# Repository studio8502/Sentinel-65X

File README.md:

# Sentinel 65X

This is a design for an 8/16-bit computer/games console, which uses
the 65816 CPU architecture (by WDC) and the VERA video system (by
Frank van den Hoef) as its core. It is not directly compatible with
any existing system, but porting from other 6502 and 65816 systems
which have a similar architecture should not prove difficult.

## Features

- Designed to minimize BOM and construction costs
- Intended to be a turnkey "fabrication ready" design which anyone
  can produce and sell for any purpose
- Fully open source hardware designs, released under the CERN OHL
  (permissive) V2
- 8MHz WDC W65C265S CPU (W65C816S compatible)
  - 16MB adress space
  - 8 timers
  - Multiple priority-encoded interrupts
  - Built-in GPIO
- 512KB of on-board static RAM
- 512KB of flash ROM
- RGB video output at 640x480
- Stereo audio output
- SD card slot
- Dual enhanced SNES-compatible controller ports
  - Supports SNES controllers & joysticks
  - Supports the SNES mouse and clones
  - Enhanced with I2C bus support for custom peripherals
- Cartridge/expansion port with full system bus, supporting ROM,
  RAM, and I/O expansions
- Amiga-inspired "clock port" which also serves as a debug port

## Hardware

The revision 0 schematic is nearly finished, approaching the production
of the first working prototypes. The goal is a limited release in 2024,
followed by a full release in 2025.

## Software

At the present time, software for this design is nonexistent. The
intention is to implement a kernel and library to support assembly
and C programming for cross-development (using the Calypsi C toolchain),
and to eventually develop or port a suite of tools for on-device
programming to be put into the system ROM.

The planned kernel will be reminiscent of the architecture of MSX-DOS
2, but will support long file names and the FAT32 (and later ExFAT)
filesystem on SD cards.

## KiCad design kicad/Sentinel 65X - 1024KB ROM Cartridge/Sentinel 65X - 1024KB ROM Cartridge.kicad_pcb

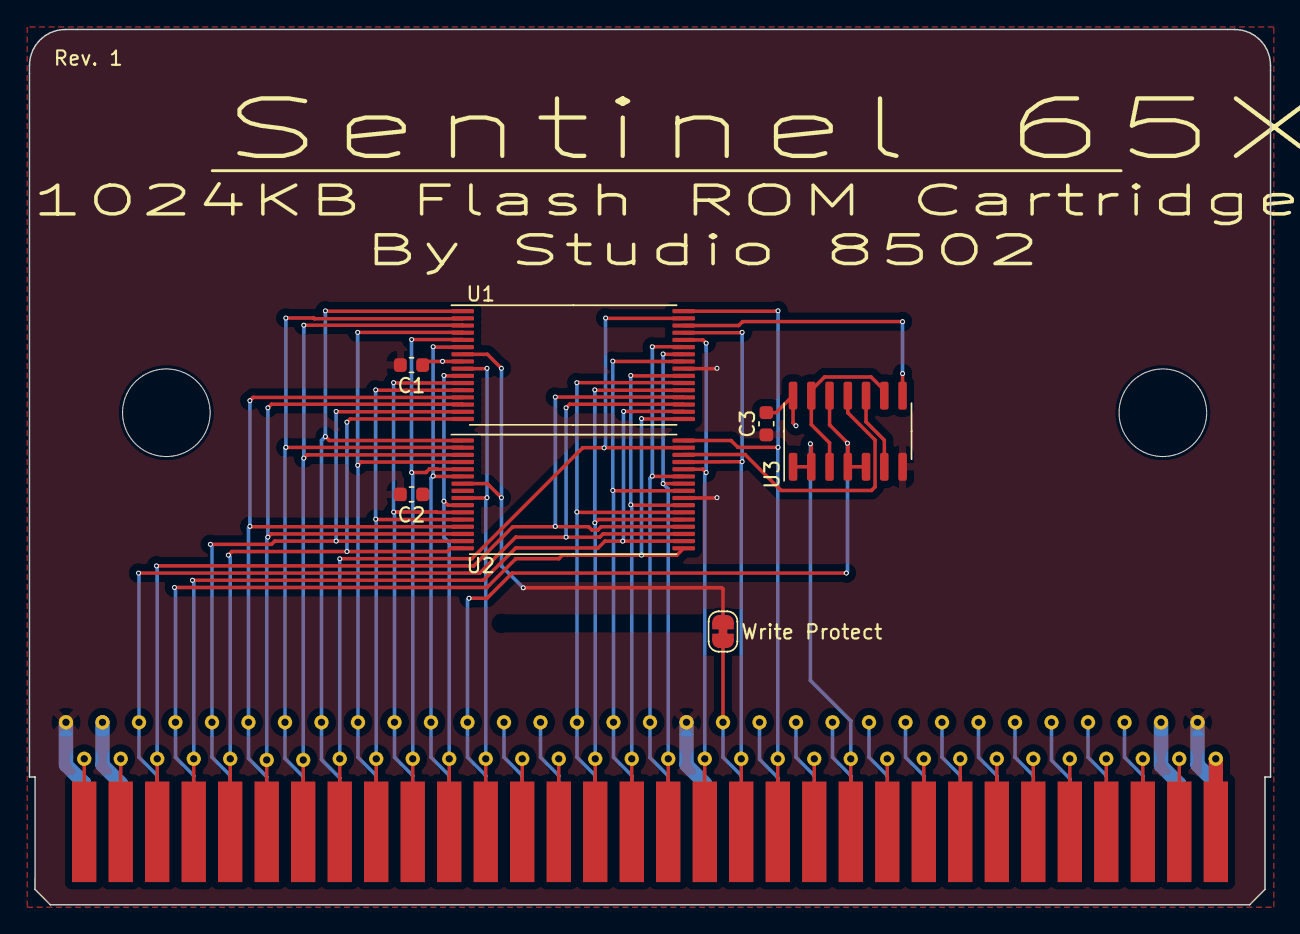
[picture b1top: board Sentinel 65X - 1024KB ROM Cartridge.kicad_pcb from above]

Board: 2 copper layers, 86.4 x 60.9 mm, 8 parts (0 on the bottom side), 38 nets.

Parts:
C1, C2, C3: 100nF; C_0603_1608Metric
J1: 2x32 2.54mm Card Edge Connector; Conn_Edge_2x32_THT_2.54mm_Male
JP1: SolderJumper_2_Bridged; SolderJumper-2_P1.3mm_Bridged_RoundedPad1.0x1.5mm
U1, U2: TSOP-I-32_14.4x8mm_P0.5mm
U3: 74LS00; SOIC-14_3.9x8.7mm_P1.27mm

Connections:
+3.3V: C1.1, C2.1, C3.1, J1.a2, J1.a31, U1.8 (VDD), U2.8 (VDD), U3.14 (VCC)
/A0: J1.b30, U1.20 (A0), U2.20 (A0)
/A1: J1.a30, U1.19 (A1), U2.19 (A1)
/A2: J1.b29, U1.18 (A2), U2.18 (A2)
/A3: J1.a29, U1.17 (A3), U2.17 (A3)
/A4: J1.b28, U1.16 (A4), U2.16 (A4)
/A5: J1.a28, U1.15 (A5), U2.15 (A5)
/A6: J1.b27, U1.14 (A6), U2.14 (A6)
/A7: J1.a27, U1.13 (A7), U2.13 (A7)
/A8: J1.b26, U1.3 (A8), U2.3 (A8)
/A9: J1.a26, U1.2 (A9), U2.2 (A9)
/A10: J1.b25, U1.31 (A10), U2.31 (A10)
/A11: J1.a25, U1.1 (A11), U2.1 (A11)
/A12: J1.b24, U1.12 (A12), U2.12 (A12)
/A13: J1.a24, U1.4 (A13), U2.4 (A13)
/A14: J1.b23, U1.5 (A14), U2.5 (A14)
/A15: J1.a23, U1.11 (A15), U2.11 (A15)
/A16: J1.b22, U1.10 (A16), U2.10 (A16)
/A17: J1.a22, U1.6 (A17), U2.6 (A17)
/A18: J1.b21, U1.9 (A18), U2.9 (A18)
/A19: J1.a21, U3.4, U3.5, U3.12
/D0: J1.b18, U1.21 (D0), U2.21 (D0)
/D1: J1.a18, U1.22 (D1), U2.22 (D1)
/D2: J1.b17, U1.23 (D2), U2.23 (D2)
/D3: J1.a17, U1.25 (D3), U2.25 (D3)
/D4: J1.b16, U1.26 (D4), U2.26 (D4)
/D5: J1.a16, U1.27 (D5), U2.27 (D5)
/D6: J1.b15, U1.28 (D6), U2.28 (D6)
/D7: J1.b14, U1.29 (D7), U2.29 (D7)
/~CS6: J1.b11, U3.1, U3.2
/~RD: J1.b13, U1.32 (~OE), U2.32 (~OE)
/~ROMH: U2.30 (~CE), U3.11
/~ROML: U1.30 (~CE), U3.8
/~WR: JP1.2 (B), U1.7 (~WE), U2.7 (~WE)
GND: C1.2, C2.2, C3.2, J1.a1, J1.a15, J1.a32, U1.24 (GND), U2.24 (GND), U3.7 (GND)
unnamed: J1.a14, JP1.1 (A)
unnamed: U3.6, U3.10
unnamed: U3.3, U3.9, U3.13

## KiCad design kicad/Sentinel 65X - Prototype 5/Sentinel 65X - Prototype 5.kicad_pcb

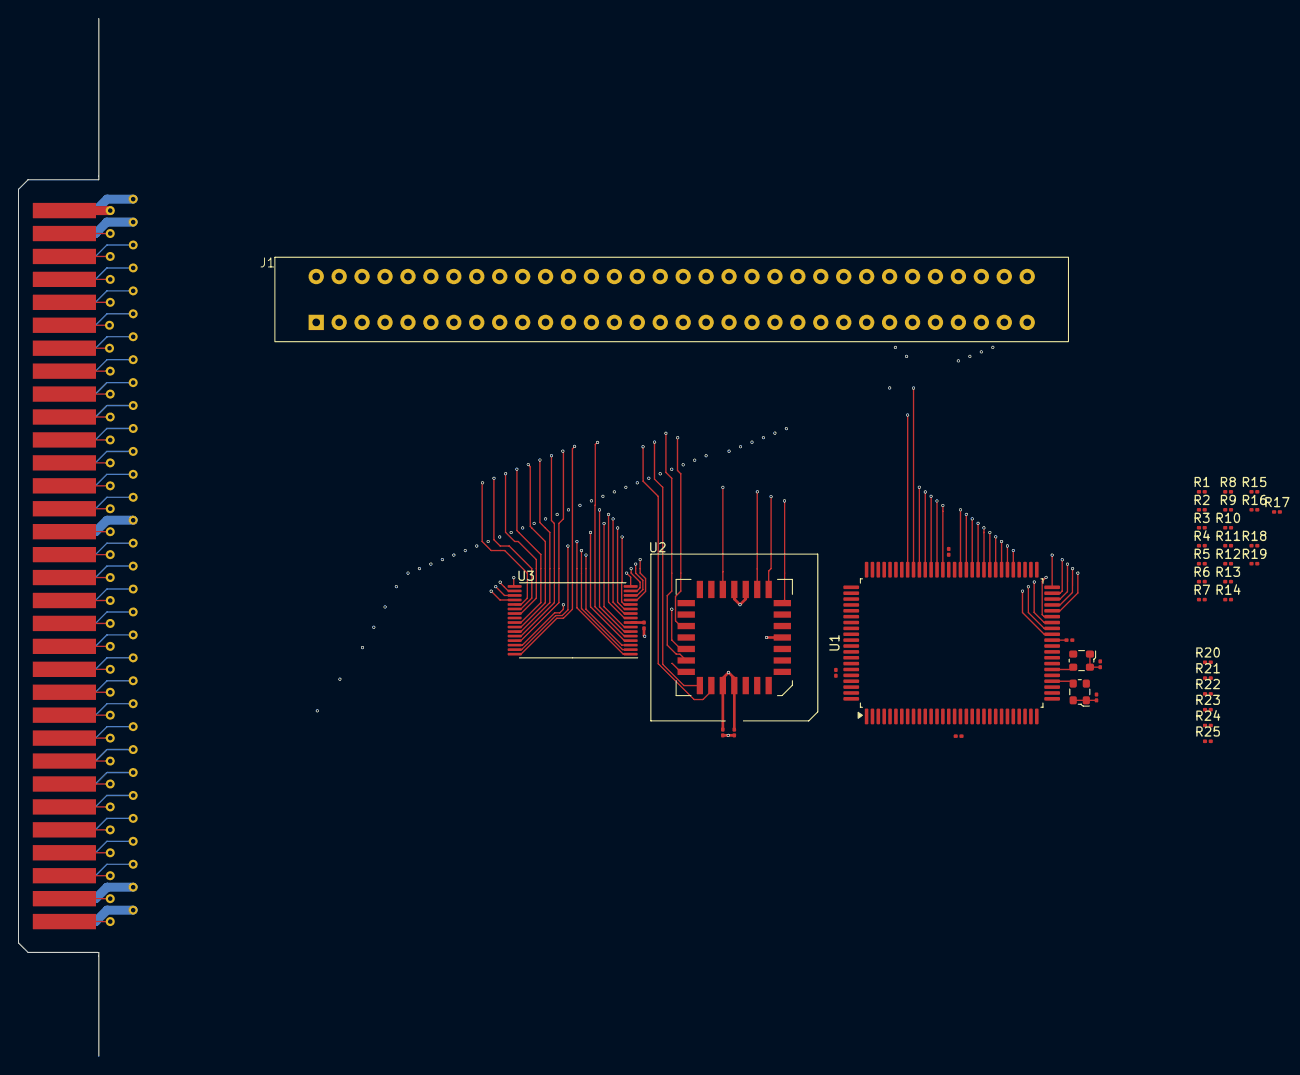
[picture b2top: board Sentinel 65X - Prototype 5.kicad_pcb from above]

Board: 6 copper layers, 41 parts (0 on the bottom side), 69 nets.

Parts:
C1, C2, C3, C4, C5, C6, C7, C8, C9: 100nF; C_0201_0603Metric
J1: 2x32 2.54mm Card Edge Connector; Conn_Edge_2x32p_THT_2.54mm_5.08mm
J2: 2x32 2.54mm Card Edge Connector; Conn_Edge_2x32_THT_2.54mm_Male
R1, R2, R3, R4, R5, R6, R7, R8, R9, R10, R11, R12, R13, R14, R15, R16, R17, R18, R19, R20, R21, R22, R23, R24, R25: 3.3KΩ; R_0201_0603Metric
U1: W65C265S8QG-8; PQFP-100_14x20mm_P0.65mm
U2: ATF22LV10C-10JU; PLCC-28_SMD-Socket
U3: IS61C5128AS-25HLI; TSOP-I-32_11.8x8mm_P0.5mm
X1: 520-327MVATX-2-CNTR3; Oscillator_SMD_ECS_2520MV-xxx-xx-4Pin_2.5x2.0mm
X2: KC2520Z8.00000C1KX00; Oscillator_SMD_ECS_2520MV-xxx-xx-4Pin_2.5x2.0mm

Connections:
+3.3V: C1.1, C2.1, C3.1, C4.1, C5.1, C6.1, C7.1, C8.1, C9.1, J1.a2, J1.a31, J2.a2, J2.a31, R1.1, R2.1, R3.1, R4.1, R5.2, R6.2, R7.2, R8.2, R9.2, R10.2, R11.2, R12.2, R13.2, R14.2, R15.2, R16.2, R17.2, R18.2, R19.2, R20.2, R21.2, R22.2, R23.2, R24.2, R25.2, U1.14 (VDD), U1.41 (VDD), U1.66 (VDD), U1.89 (VDD), U2.1 (VCC), U2.28 (VCC), U3.8 (VDD), X1.1 (EN), X1.4 (V+), X2.1 (EN), X2.4 (V+)
+5V: J1.b32, J2.b32
/A0: J1.b3, J2.b3, U1.42 (A0), U3.20 (A0)
/A1: J1.a3, J2.a3, U1.43 (A1), U3.19 (A1)
/A2: J1.b4, J2.b4, U1.44 (A2), U3.18 (A2)
/A3: J1.a4, J2.a4, U1.45 (A3), U3.17 (A3)
/A4: J1.b5, J2.b5, U1.46 (A4), U3.16 (A4)
/A5: J1.a5, J2.a5, U1.47 (A5), U3.15 (A5)
/A6: J1.b6, J2.b6, U1.48 (A6), U3.14 (A6)
/A7: J1.a6, J2.a6, U1.49 (A7), U3.13 (A7)
/A8: J1.b7, J2.b7, U1.50 (A8), U3.3 (A8)
/A9: J1.a7, J2.a7, U1.55 (A9), U3.2 (A9)
/A10: J1.b8, J2.b8, U1.56 (A10), U3.31 (A10)
/A11: J1.a8, J2.a8, U1.57 (A11), U3.1 (A11)
/A12: J1.b9, J2.b9, U1.58 (A12), U3.12 (A12)
/A13: J1.a9, J2.a9, U1.59 (A13), U3.4 (A13)
/A14: J1.b10, J2.b10, U1.60 (A14), U3.11 (A14)
/A15: J1.a10, J2.a10, U1.61 (A15), U3.7 (A15)
/A16: J1.b11, J2.b11, U1.62 (A16), U3.10 (A16)
/A17: J1.a11, J2.a11, U1.63 (A17), U3.9 (A17)
/A18: J1.b12, J2.b12, U1.64 (A18), U3.6 (A18)
/A19: J1.a12, J2.a12, U1.67 (A19), U2.10 (IN)
/A20: J1.b13, J2.b13, U1.68 (A20), U2.11 (IN)
/A21: J1.a13, J2.a13, U1.69 (A21), U2.12 (IN)
/A22: J1.b14, J2.b14, U1.70 (A22), U2.13 (IN)
/A23: J1.a14, J2.a14, U1.71 (A23), U2.16 (IN)
/BA: J1.b24, J2.b24, R6.1, U1.39 (BA)
/BE: J1.a21, J2.a21, R4.2, U1.35 (BE)
/CDONE: R15.1, U1.99 (P43)
/CLK: U1.36 (CLK), X1.3 (OUT)
/D0: J1.b15, J2.b15, U1.84 (D0), U3.21 (I/O0)
/D1: J1.a15, J2.a15, U1.85 (D1), U3.22 (I/O1)
/D2: J1.b16, J2.b16, U1.86 (D2), U3.23 (I/O2)
/D3: J1.a16, J2.a16, U1.87 (D3), U3.25 (I/O3)
/D4: J1.b17, J2.b17, U1.88 (D4), U3.26 (I/O4)
/D5: J1.a17, J2.a17, U1.91 (D5), U3.27 (I/O5)
/D6: J1.b18, J2.b18, U1.92 (D6), U3.28 (I/O6)
/D7: J1.b19, J2.b19, U1.93 (D7), U3.29 (I/O7)
/FCLK: U1.34 (FCLK), X2.3 (OUT)
/I2C_SCL: J1.a27, J2.a27, R17.1, U1.7 (P47)
/I2C_SDA: J1.a28, J2.a28, R16.1, U1.6 (P46)
/PHI2: J1.b1, J2.b1, U1.38 (PHI2), U2.2 (CLK/IN)
/RUN: J1.a23, J2.a23, R5.1, U1.32 (RUN)
/R/~W: J1.b25, J2.b25, R7.1, U1.31 (~WE), U2.3 (IN)
/SNES_CLK: J1.a30, J2.a30, U1.8 (P50)
/SNES_DATA0: J1.b27, J2.b27, U1.10 (P52)
/SNES_DATA1: J1.b28, J2.b28, U1.11 (P53)
/SNES_DATA2: J1.b29, J2.b29
/SNES_DATA3: J1.b30, J2.b30
/SNES_LATCH: J1.a29, J2.a29, U1.9 (P51)
/~BOOT_SEL: R18.1, U1.21 (P63)
/~CS4: R10.1, U1.80 (~CS4), U2.9 (IN)
/~CS5: R11.1, U1.81 (~CS5), U2.7 (IN)
/~CS6: J1.b22, J2.b22, R12.1, U1.82 (~CS6), U2.6 (IN)
/~CS7: J1.a22, J2.a22, R13.1, U1.83 (~CS7)
/~FPGA_RESET: R14.1, U1.98 (P42)
/~IRQ: J1.a24, J2.a24, R2.2, U1.97 (~IRQ)
/~I/O0: J1.b26, J2.b26, R8.1, U1.72 (~CS0)
/~I/O1: J1.b23, J2.b23, R9.1, U1.73 (~CS1)
/~NMI: J1.a26, J2.a26, R3.2, U1.96 (~NMI)
/~RAM0: R21.1, U2.23 (I/O), U3.30 (~CE)
/~RAM1: J1.a20, J2.a20, R20.1, U2.21 (I/O)
/~RD: J1.b20, J2.b20, R24.1, U2.26 (I/O), U3.5 (~WE)
/~RES: J1.b2, J2.b2, R1.2, U1.26 (~RES)
/~ROM0: R23.1, U2.25 (I/O)
/~ROM1: J1.b21, J2.b21, R22.1, U2.24 (I/O)
/~VIRQ: J1.a25, J2.a25, R19.1, U1.22 (P64)
/~WR: J1.a19, J2.a19, R25.1, U2.27 (I/O), U3.32 (~OE)
GND: C1.2, C2.2, C3.2, C4.2, C5.2, C6.2, C7.2, C8.2, C9.2, J1.a1, J1.a18, J1.a32, J2.a1, J2.a18, J2.a32, U1.15 (VSS), U1.40 (VSS), U1.65 (VSS), U1.90 (VSS), U2.8 (GND), U2.14 (GND), U2.15 (GND), U2.22 (GND), U3.24 (GND), X1.2 (GND), X2.2 (GND)

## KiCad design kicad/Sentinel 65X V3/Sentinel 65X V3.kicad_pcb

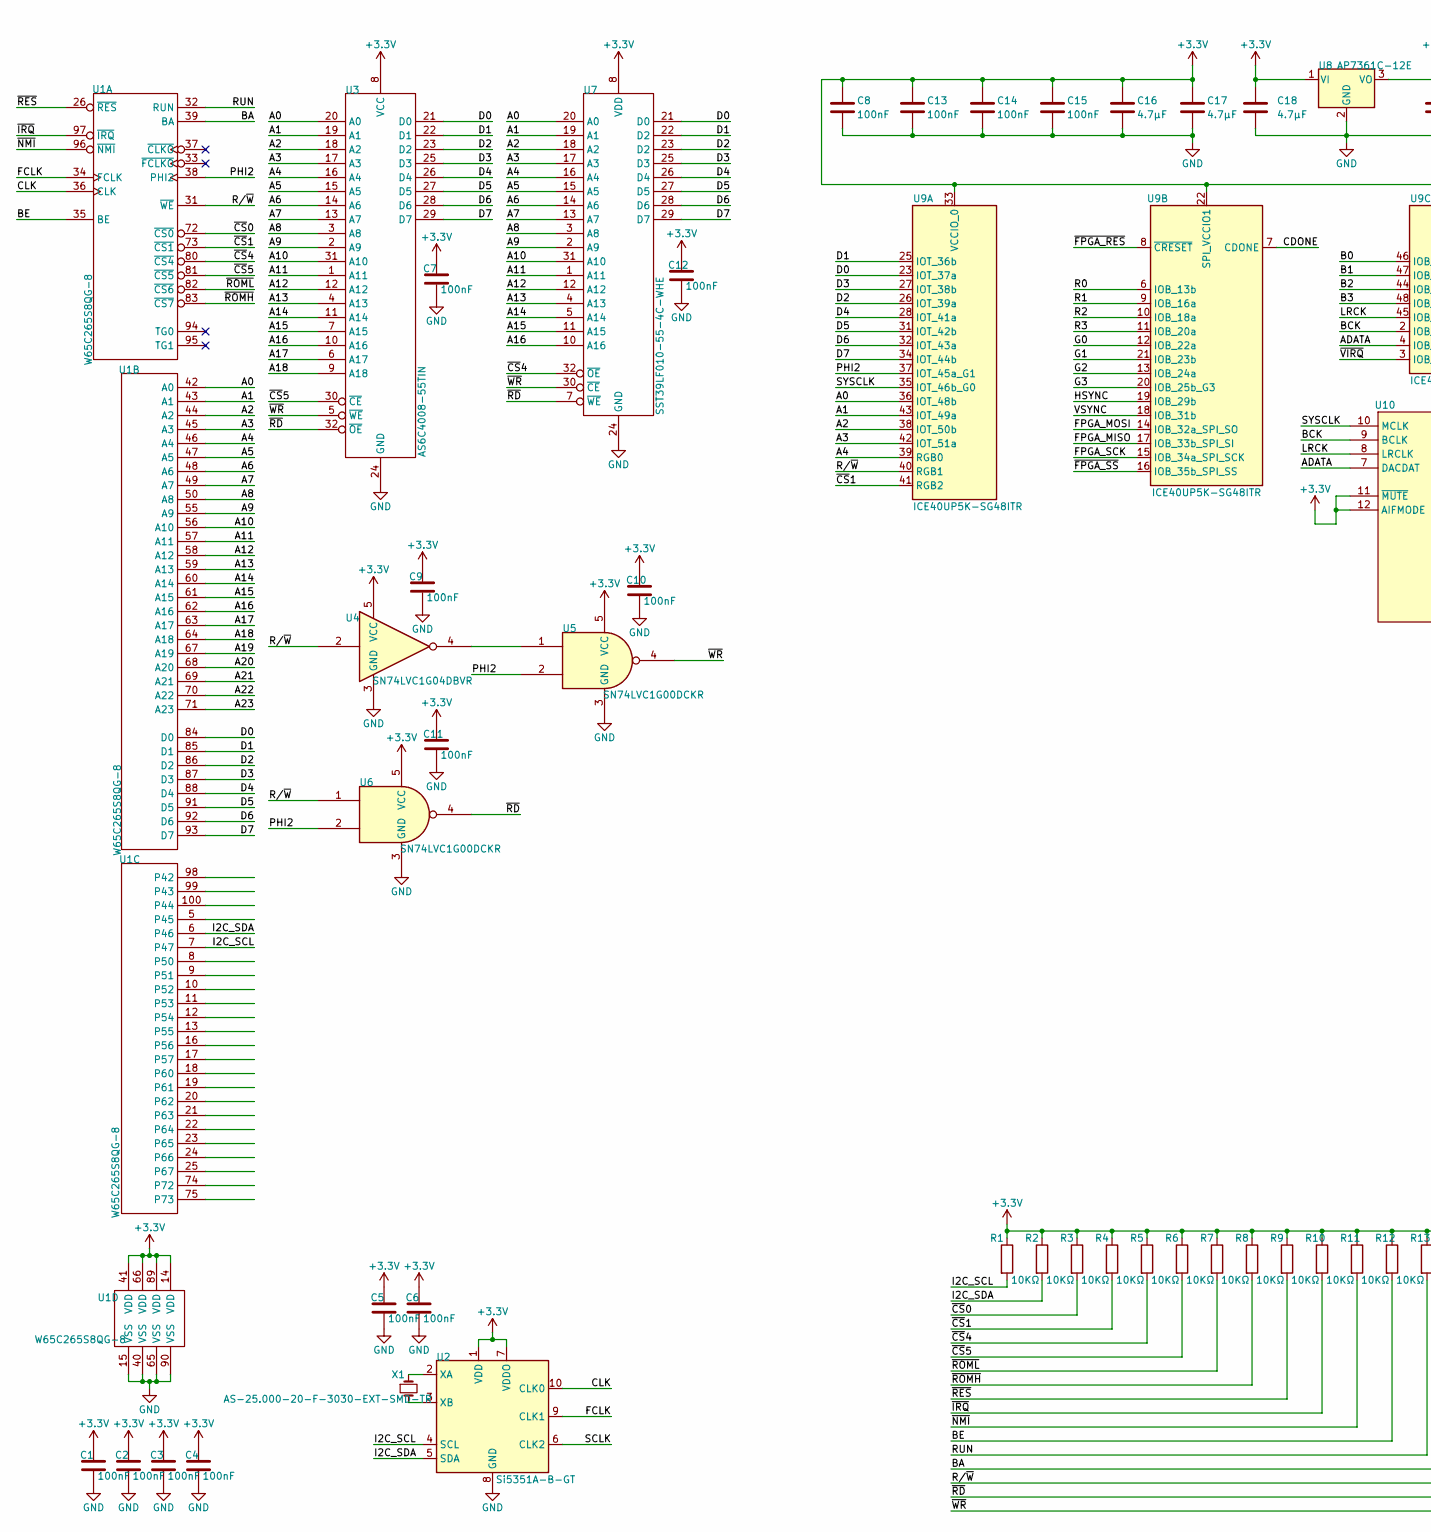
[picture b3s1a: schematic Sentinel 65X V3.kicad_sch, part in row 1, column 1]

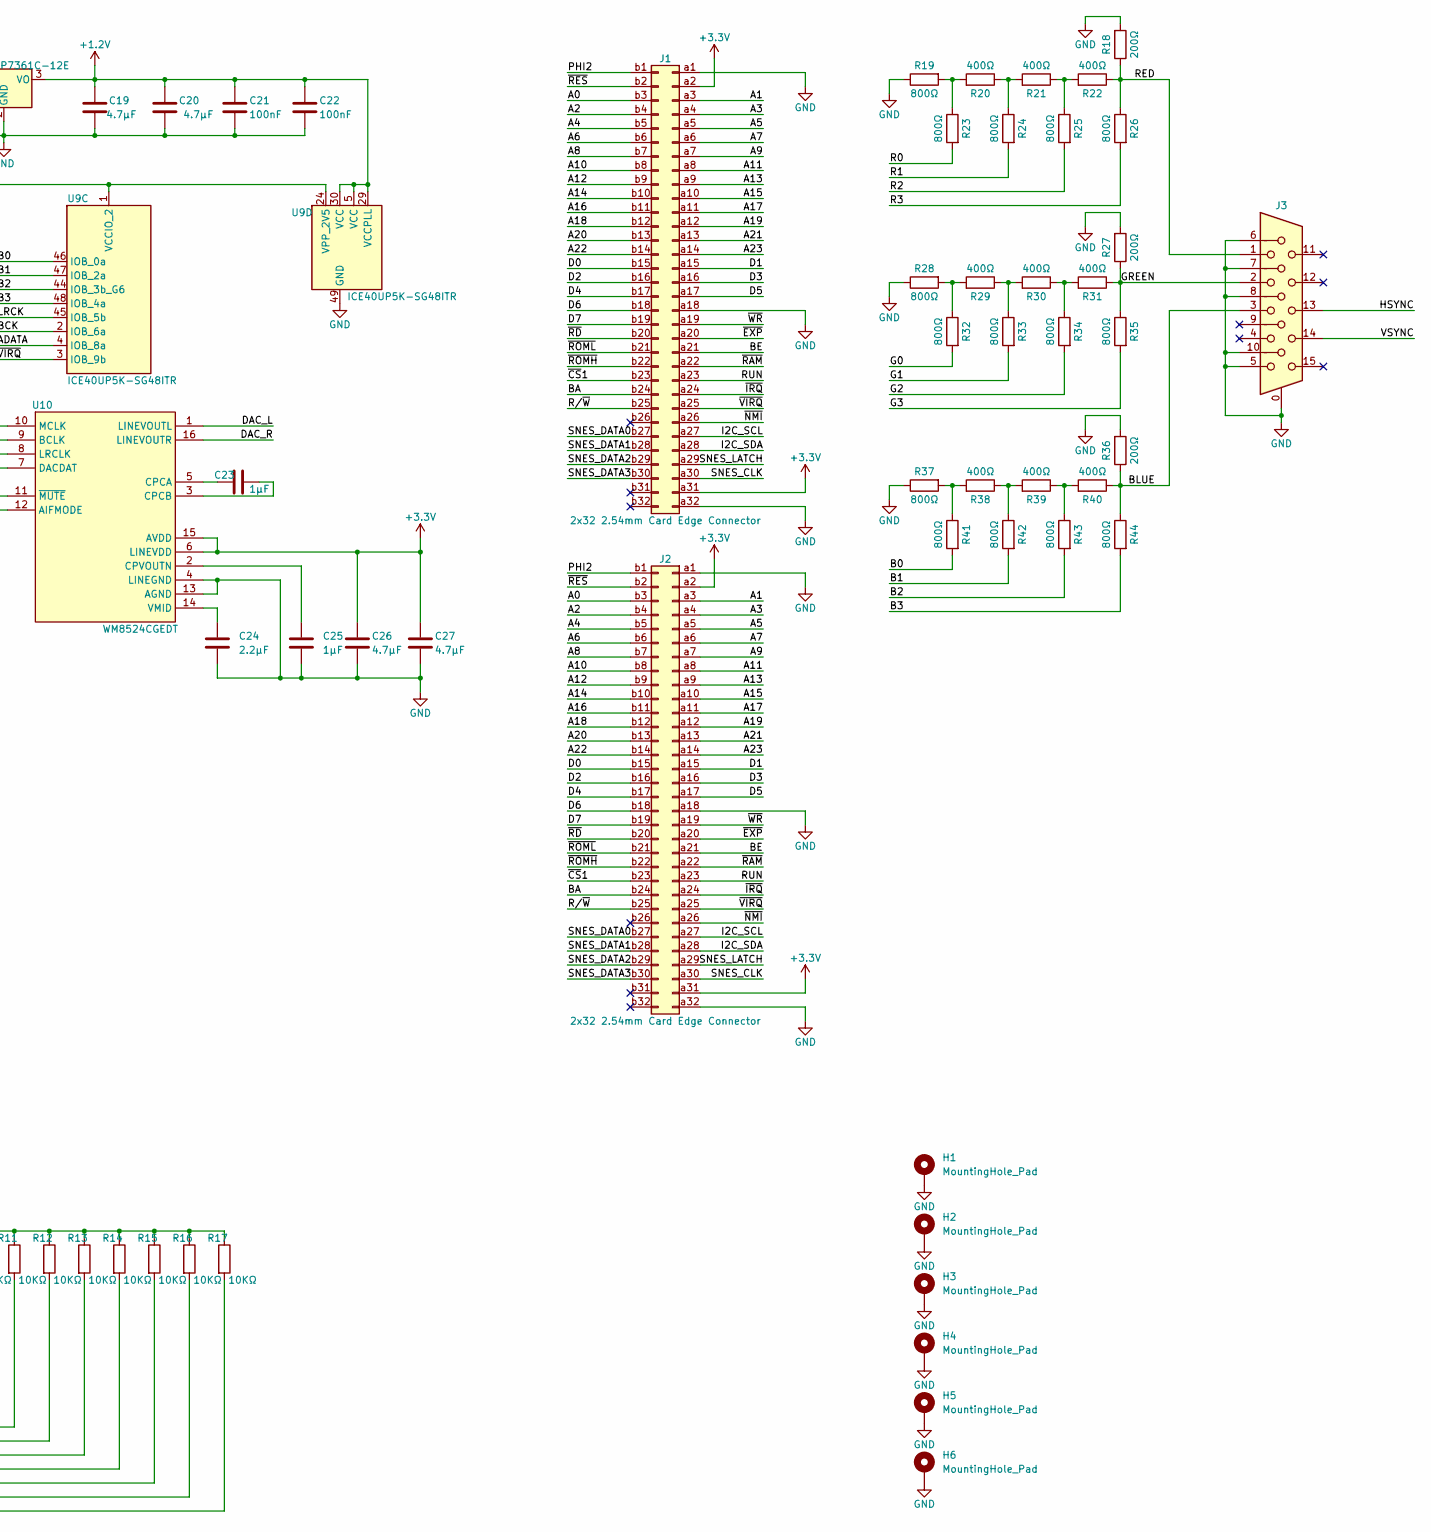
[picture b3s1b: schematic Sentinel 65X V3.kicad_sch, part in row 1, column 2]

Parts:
C1, C2, C3, C4, C5, C6, C7, C9, C10, C11, C12: 100nF; C_01005_0402Metric
C8, C13, C14, C15, C21, C22: 100nF; C_0402_1005Metric
C16, C17, C18, C19, C20, C26, C27: 4.7µF; C_0402_1005Metric
C23, C25: 1µF; C_0402_1005Metric
C24: 2.2µF; C_0402_1005Metric
H1, H2, H3, H4, H5, H6: MountingHole_Pad; MountingHole_3.7mm
J1: 2x32 2.54mm Card Edge Connector; Conn_Edge_2x32p_THT_2.54mm_5.08mm
J2: 2x32 2.54mm Card Edge Connector; Conn_Edge_2x32_THT_2.54mm_Male
J3: SVGA Connector; DSUB-15-HD_Female_Horizontal_P2.29x1.98mm_EdgePinOffset3.03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
R1, R2, R3, R4, R5, R6, R7, R8, R9, R10, R11, R12, R13, R14, R15, R16, R17: 10KΩ; R_0402_1005Metric
R18, R27, R36: 200Ω; R_0402_1005Metric
R19, R23, R24, R25, R26, R28, R32, R33, R34, R35, R37, R41, R42, R43, R44: 800Ω; R_0402_1005Metric
R20, R21, R22, R29, R30, R31, R38, R39, R40: 400Ω; R_0402_1005Metric
U1: W65C265S8QG-8; TQFP-100_14x14mm_P0.5mm
U2: Si5351A-B-GT; MSOP-10_3x3mm_P0.5mm
U3: AS6C4008-55TIN; TSOP-I-32_18.4x8mm_P0.5mm
U4: SN74LVC1G04DBVR; SOT-23-5
U5, U6: SN74LVC1G00DCKR; SOT-23-5
U7: SST39LF010-55-4C-WHE; TSOP-I-32_14.4x8mm_P0.5mm
U8: AP7361C-12E; SOT-223-3_TabPin2
U9: ICE40UP5K-SG48ITR; QFN-48-1EP_7x7mm_P0.5mm_EP5.6x5.6mm
U10: WM8524CGEDT; TSSOP-16_4.4x5mm_P0.65mm
X1: AS-25.000-20-F-3030-EXT-SMD-TR; Crystal_SMD_HC49-SD

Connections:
+1V2: C19.1, C20.1, C21.1, C22.1, U8.3 (VO), U9.5 (VCC), U9.29 (VCCPLL), U9.30 (VCC)
+3.3V: C1.1, C2.1, C3.1, C4.1, C5.1, C6.1, C7.1, C8.1, C9.1, C10.1, C11.1, C12.1, C13.1, C14.1, C15.1, C16.1, C17.1, C18.1, C26.1, C27.1, J1.a2, J1.a31, J2.a2, J2.a31, R1.1, R2.1, R3.1, R4.1, R5.1, R6.1, R7.1, R8.1, R9.1, R10.1, R11.1, R12.1, R13.1, R14.1, R15.1, R16.1, R17.1, U1.14 (VDD), U1.41 (VDD), U1.66 (VDD), U1.89 (VDD), U2.1 (VDD), U2.7 (VDDO), U3.8 (VCC), U4.5 (VCC), U5.5 (VCC), U6.5 (VCC), U7.8 (VDD), U8.1 (VI), U9.1 (VCCIO_2), U9.22 (SPI_VCCIO1), U9.24 (VPP_2V5), U9.33 (VCCIO_0), U10.6 (LINEVDD), U10.11 (~MUTE), U10.12 (AIFMODE), U10.15 (AVDD)
/A0: J1.b3, J2.b3, U1.42 (A0), U3.20 (A0), U7.20 (A0), U9.36 (IOT_48b)
/A1: J1.a3, J2.a3, U1.43 (A1), U3.19 (A1), U7.19 (A1), U9.43 (IOT_49a)
/A2: J1.b4, J2.b4, U1.44 (A2), U3.18 (A2), U7.18 (A2), U9.38 (IOT_50b)
/A3: J1.a4, J2.a4, U1.45 (A3), U3.17 (A3), U7.17 (A3), U9.42 (IOT_51a)
/A4: J1.b5, J2.b5, U1.46 (A4), U3.16 (A4), U7.16 (A4), U9.39 (RGB0)
/A5: J1.a5, J2.a5, U1.47 (A5), U3.15 (A5), U7.15 (A5)
/A6: J1.b6, J2.b6, U1.48 (A6), U3.14 (A6), U7.14 (A6)
/A7: J1.a6, J2.a6, U1.49 (A7), U3.13 (A7), U7.13 (A7)
/A8: J1.b7, J2.b7, U1.50 (A8), U3.3 (A8), U7.3 (A8)
/A9: J1.a7, J2.a7, U1.55 (A9), U3.2 (A9), U7.2 (A9)
/A10: J1.b8, J2.b8, U1.56 (A10), U3.31 (A10), U7.31 (A10)
/A11: J1.a8, J2.a8, U1.57 (A11), U3.1 (A11), U7.1 (A11)
/A12: J1.b9, J2.b9, U1.58 (A12), U3.12 (A12), U7.12 (A12)
/A13: J1.a9, J2.a9, U1.59 (A13), U3.4 (A13), U7.4 (A13)
/A14: J1.b10, J2.b10, U1.60 (A14), U3.11 (A14), U7.5 (A14)
/A15: J1.a10, J2.a10, U1.61 (A15), U3.7 (A15), U7.11 (A15)
/A16: J1.b11, J2.b11, U1.62 (A16), U3.10 (A16), U7.10 (A16)
/A17: J1.a11, J2.a11, U1.63 (A17), U3.6 (A17)
/A18: J1.b12, J2.b12, U1.64 (A18), U3.9 (A18)
/A19: J1.a12, J2.a12, U1.67 (A19)
/A20: J1.b13, J2.b13, U1.68 (A20)
/A21: J1.a13, J2.a13, U1.69 (A21)
/A22: J1.b14, J2.b14, U1.70 (A22)
/A23: J1.a14, J2.a14, U1.71 (A23)
/ADATA: U9.4 (IOB_8a), U10.7 (DACDAT)
/B0: R41.2, U9.46 (IOB_0a)
/B1: R42.2, U9.47 (IOB_2a)
/B2: R43.2, U9.44 (IOB_3b_G6)
/B3: R44.2, U9.48 (IOB_4a)
/BA: J1.b24, J2.b24, R14.2, U1.39 (BA)
/BCK: U9.2 (IOB_6a), U10.9 (BCLK)
/BE: J1.a21, J2.a21, R12.2, U1.35 (BE)
/BLUE: J3.3, R36.1, R40.1, R44.1
/CDONE: U9.7 (CDONE)
/CLK: U1.36 (CLK), U2.10 (CLK0)
/D0: J1.b15, J2.b15, U1.84 (D0), U3.21 (D0), U7.21 (D0), U9.23 (IOT_37a)
/D1: J1.a15, J2.a15, U1.85 (D1), U3.22 (D1), U7.22 (D2), U9.25 (IOT_36b)
/D2: J1.b16, J2.b16, U1.86 (D2), U3.23 (D2), U7.23 (D2), U9.26 (IOT_39a)
/D3: J1.a16, J2.a16, U1.87 (D3), U3.25 (D3), U7.25 (D3), U9.27 (IOT_38b)
/D4: J1.b17, J2.b17, U1.88 (D4), U3.26 (D4), U7.26 (D4), U9.28 (IOT_41a)
/D5: J1.a17, J2.a17, U1.91 (D5), U3.27 (D5), U7.27 (D5), U9.31 (IOT_42b)
/D6: J1.b18, J2.b18, U1.92 (D6), U3.28 (D6), U7.28 (D6), U9.32 (IOT_43a)
/D7: J1.b19, J2.b19, U1.93 (D7), U3.29 (D7), U7.29 (D7), U9.34 (IOT_44b)
/DAC_L: U10.1 (LINEVOUTL)
/DAC_R: U10.16 (LINEVOUTR)
/FCLK: U1.34 (FCLK), U2.9 (CLK1)
/FPGA_MISO: U9.17 (IOB_33b_SPI_SI)
/FPGA_MOSI: U9.14 (IOB_32a_SPI_SO)
/FPGA_SCK: U9.15 (IOB_34a_SPI_SCK)
/G0: R32.2, U9.12 (IOB_22a)
/G1: R33.2, U9.21 (IOB_23b)
/G2: R34.2, U9.13 (IOB_24a)
/G3: R35.2, U9.20 (IOB_25b_G3)
/GREEN: J3.2, R27.1, R31.1, R35.1
/HSYNC: J3.13, U9.19 (IOB_29b)
/I2C_SCL: J1.a27, J2.a27, R1.2, U1.7 (P47), U2.4 (SCL)
/I2C_SDA: J1.a28, J2.a28, R2.2, U1.6 (P46), U2.5 (SDA)
/LRCK: U9.45 (IOB_5b), U10.8 (LRCLK)
/PHI2: J1.b1, J2.b1, U1.38 (PHI2), U5.2, U6.2, U9.37 (IOT_45a_G1)
/R0: R23.2, U9.6 (IOB_13b)
/R1: R24.2, U9.9 (IOB_16a)
/R2: R25.2, U9.10 (IOB_18a)
/R3: R26.2, U9.11 (IOB_20a)
/RED: J3.1, R18.1, R22.1, R26.1
/RUN: J1.a23, J2.a23, R13.2, U1.32 (RUN)
/R/~W: J1.b25, J2.b25, R15.2, U1.31 (~WE), U4.2, U6.1, U9.40 (RGB1)
/SCLK: U2.6 (CLK2)
/SNES_CLK: J1.a30, J2.a30
/SNES_DATA0: J1.b27, J2.b27
/SNES_DATA1: J1.b28, J2.b28
/SNES_DATA2: J1.b29, J2.b29
/SNES_DATA3: J1.b30, J2.b30
/SNES_LATCH: J1.a29, J2.a29
/SYSCLK: U9.35 (IOT_46b_G0), U10.10 (MCLK)
/VSYNC: J3.14, U9.18 (IOB_31b)
/~CS0: R3.2, U1.72 (~CS0)
/~CS1: J1.b23, J2.b23, R4.2, U1.73 (~CS1), U9.41 (RGB2)
/~CS4: R5.2, U1.80 (~CS4), U7.32 (~OE)
/~CS5: R6.2, U1.81 (~CS5), U3.30 (~CE)
/~EXP: J1.a20, J2.a20
/~FPGA_RES: U9.8 (~CRESET)
/~FPGA_SS: U9.16 (IOB_35b_SPI_SS)
/~IRQ: J1.a24, J2.a24, R10.2, U1.97 (~IRQ)
/~NMI: J1.a26, J2.a26, R11.2, U1.96 (~NMI)
/~RAM: J1.a22, J2.a22
/~RD: J1.b20, J2.b20, R16.2, U3.32 (~OE), U6.4, U7.7 (~WE)
/~RES: J1.b2, J2.b2, R9.2, U1.26 (~RES)
/~ROMH: J1.b22, J2.b22, R8.2, U1.83 (~CS7)
/~ROML: J1.b21, J2.b21, R7.2, U1.82 (~CS6)
/~VIRQ: J1.a25, J2.a25, U9.3 (IOB_9b)
/~WR: J1.a19, J2.a19, R17.2, U3.5 (~WE), U5.4, U7.30 (~CE)
GND: C1.2, C2.2, C3.2, C4.2, C5.2, C6.2, C7.2, C8.2, C9.2, C10.2, C11.2, C12.2, C13.2, C14.2, C15.2, C16.2, C17.2, C18.2, C19.2, C20.2, C21.2, C22.2, C24.2, C25.2, C26.2, C27.2, H1.1, H2.1, H3.1, H4.1, H5.1, H6.1, J1.a1, J1.a18, J1.a32, J2.a1, J2.a18, J2.a32, J3.0, J3.5, J3.6, J3.7, J3.8, J3.10, R18.2, R19.1, R27.2, R28.1, R36.2, R37.1, U1.15 (VSS), U1.40 (VSS), U1.65 (VSS), U1.90 (VSS), U2.8 (GND), U3.24 (GND), U4.3 (GND), U5.3 (GND), U6.3 (GND), U7.24 (GND), U8.2 (GND), U9.49 (GND), U10.4 (LINEGND), U10.13 (AGND)
unnamed: R19.2, R20.2, R23.1
unnamed: R20.1, R21.2, R24.1
unnamed: R21.1, R22.2, R25.1
unnamed: R28.2, R29.2, R32.1
unnamed: R29.1, R30.2, R33.1
unnamed: R30.1, R31.2, R34.1
unnamed: R37.2, R38.2, R41.1
unnamed: R38.1, R39.2, R42.1
unnamed: R39.1, R40.2, R43.1
unnamed: U2.2 (XA), X1.1
unnamed: U2.3 (XB), X1.2
unnamed: U4.4, U5.1
unnamed: C23.2, U10.5 (CPCA)
unnamed: C23.1, U10.3 (CPCB)
unnamed: C25.1, U10.2 (CPVOUTN)
unnamed: C24.1, U10.14 (VMID)

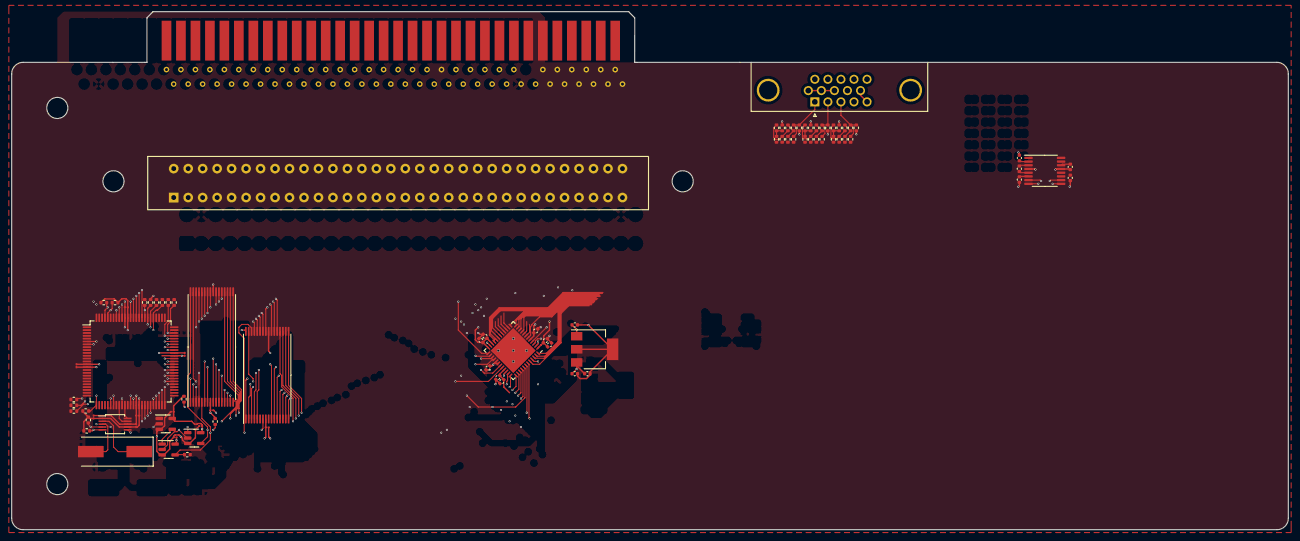
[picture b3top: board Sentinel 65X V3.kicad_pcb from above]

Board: 6 copper layers, 224.0 x 90.9 mm, 91 parts (0 on the bottom side), 101 nets.

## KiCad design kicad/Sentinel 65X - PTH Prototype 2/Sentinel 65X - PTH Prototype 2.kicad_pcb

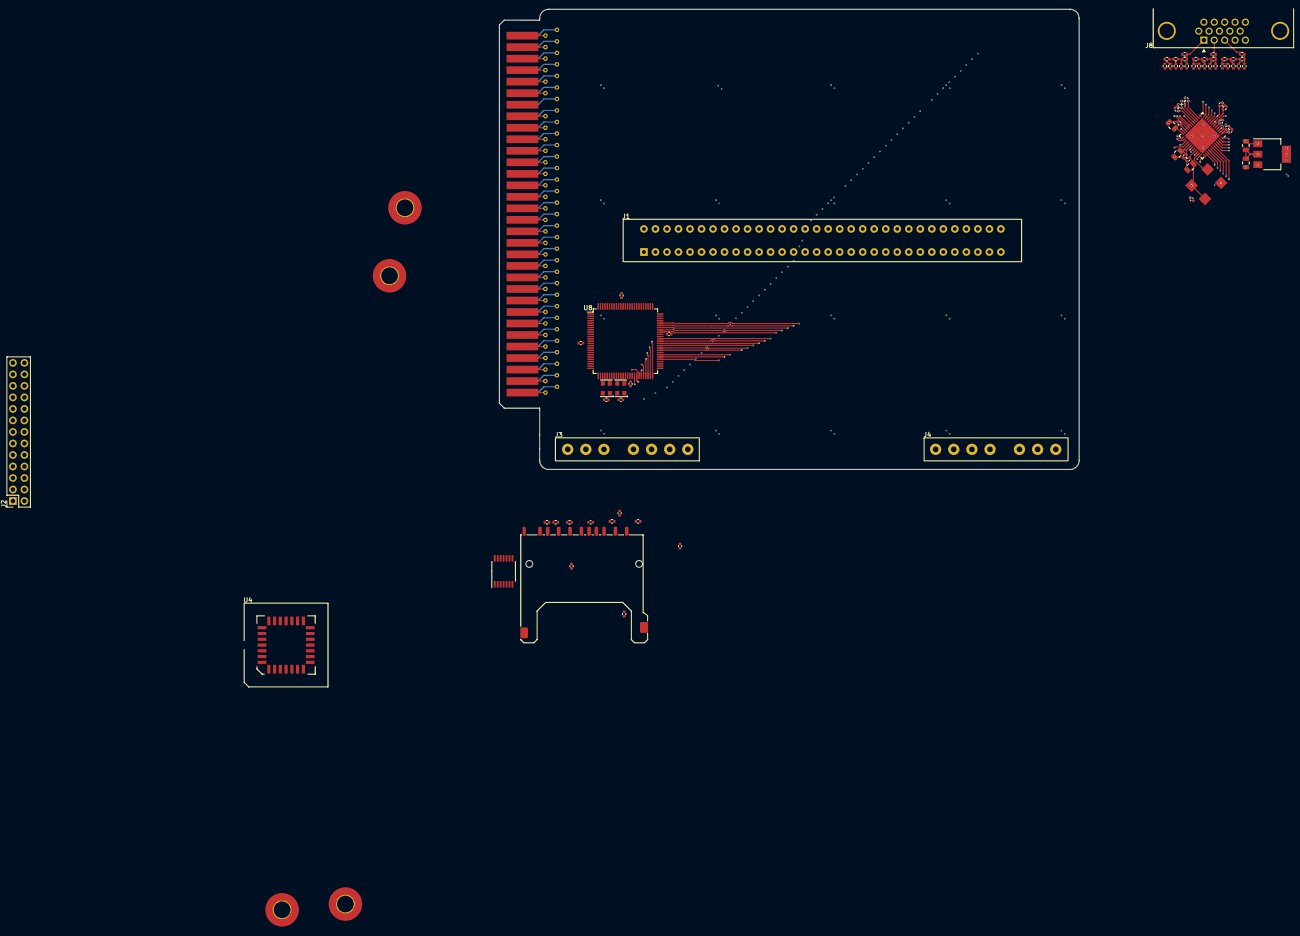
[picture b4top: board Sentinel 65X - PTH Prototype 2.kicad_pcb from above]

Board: 6 copper layers, 127.9 x 101.5 mm, 80 parts (0 on the bottom side), 107 nets.

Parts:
C1, C2, C3, C4, C5, C7, C9, C10, C11, C12, C18, C19, C20, C21, C22, C24: 100nF; C_0402_1005Metric
C13, C14, C15, C16, C17: 4.7µF; C_0805_2012Metric
C23: 4.7µF; C_0402_1005Metric
H1, H2, H3, H4: MountingHole_Pad; MountingHole_3.7mm_Pad_TopBottom
J1: 2x32 2.54mm Card Edge Connector; Conn_Edge_2x32p_THT_2.54mm_5.08mm
J2: Conn_02x13_Counter_Clockwise; PinSocket_2x13_P2.54mm_Vertical
J3: Controller 1; SNES Controller Port (Female, 90º, THT)
J4: Controller 2; SNES Controller Port (Female, 90º, THT)
J5: 2x32 2.54mm Card Edge Connector; Conn_Edge_2x32_THT_2.54mm_Male
J7: SD_Card; SD_Kyocera_145638009211859+
J8: SVGA Connector; DSUB-15-HD_Female_Horizontal_P2.29x1.98mm_EdgePinOffset3.03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
R1, R2, R3, R4, R5, R6: 10kΩ; R_0402_1005Metric
R7, R8, R9, R10, R11, R12: 47kΩ; R_0402_1005Metric
R13, R22, R31: 200Ω; R_0402_1005Metric
R14, R18, R19, R20, R21, R23, R27, R28, R29, R30, R32, R36, R37, R38, R39: 800Ω; R_0402_1005Metric
R15, R16, R17, R24, R25, R26, R33, R34, R35: 400Ω; R_0402_1005Metric
U4: ATF22LV10C-10JU; PLCC-28_SMD-Socket
U5: AP7361C-12E; SOT-223-3_TabPin2
U6: ICE40UP5K-SG48ITR; QFN-48-1EP_7x7mm_P0.5mm_EP5.6x5.6mm
U7: 74CBTLV3126PW,118; TSSOP-14_4.4x5mm_P0.65mm
U8: W65C265S8QG-8; TQFP-100_14x14mm_P0.5mm
X1: 25MHz; Oscillator_SMD_EuroQuartz_XO91-4Pin_7.0x5.0mm
X2: 32.768KHz; Oscillator_SMD_EuroQuartz_XO32-4Pin_3.2x2.5mm
X3: ASE-8.000MHZ-E-T; Oscillator_SMD_EuroQuartz_XO32-4Pin_3.2x2.5mm

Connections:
+1V2: C16.1, C17.1, C18.1, C19.1, U5.3 (VO), U6.5 (VCC), U6.29 (VCCPLL), U6.30 (VCC)
+3.3V: C1.1, C2.1, C3.1, C4.1, C5.1, C7.1, C9.1, C10.1, C11.1, C12.1, C13.1, C14.1, C15.1, C20.1, C21.1, C22.1, C23.2, C24.1, J1.a2, J1.a31, J2.26, J3.1, J4.1, J5.a2, J5.a31, J7.4 (VDD), R1.1, R2.1, R3.1, R4.1, R6.1, R7.1, R8.1, R9.1, R10.1, R11.1, U4.1 (VCC), U4.28 (VCC), U5.1 (VI), U6.1 (VCCIO_2), U6.22 (SPI_VCCIO1), U6.24 (VPP_2V5), U6.33 (VCCIO_0), U7.14 (VCC), U8.14 (VDD), U8.41 (VDD), U8.66 (VDD), U8.89 (VDD), X1.1 (EN), X1.4 (V+), X2.1 (EN), X2.4 (V+), X3.1 (EN), X3.4 (V+)
/A0: J1.b3, J2.18, J5.b3, U6.36 (IOT_48b), U8.42 (A0)
/A1: J1.a3, J2.9, J5.a3, U6.43 (IOT_49a), U8.43 (A1)
/A2: J1.b4, J2.19, J5.b4, U6.38 (IOT_50b), U8.44 (A2)
/A3: J1.a4, J2.8, J5.a4, U6.42 (IOT_51a), U8.45 (A3)
/A4: J1.b5, J5.b5, U6.39 (RGB0), U8.46 (A4)
/A5: J1.a5, J5.a5, U8.47 (A5)
/A6: J1.b6, J5.b6, U8.48 (A6)
/A7: J1.a6, J5.a6, U8.49 (A7)
/A8: J1.b7, J5.b7, U8.50 (A8)
/A9: J1.a7, J5.a7, U8.55 (A9)
/A10: J1.b8, J5.b8, U8.56 (A10)
/A11: J1.a8, J5.a8, U8.57 (A11)
/A12: J1.b9, J5.b9, U8.58 (A12)
/A13: J1.a9, J5.a9, U8.59 (A13)
/A14: J1.b10, J5.b10, U8.60 (A14)
/A15: J1.a10, J5.a10, U8.61 (A15)
/A16: J1.b11, J5.b11, U8.62 (A16)
/A17: J1.a11, J5.a11, U8.63 (A17)
/A18: J1.b12, J5.b12, U8.64 (A18)
/A19: J1.a12, J5.a12, U4.6 (IN), U8.67 (A19)
/A20: J1.b13, J5.b13, U4.7 (IN), U8.68 (A20)
/A21: J1.a13, J5.a13, U4.9 (IN), U8.69 (A21)
/A22: J1.b14, J5.b14, U4.10 (IN), U8.70 (A22)
/A23: J1.a14, J5.a14, U4.11 (IN), U8.71 (A23)
/B0: R36.2, U6.46 (IOB_0a)
/B1: R37.2, U6.47 (IOB_2a)
/B2: R38.2, U6.44 (IOB_3b_G6)
/B3: R39.2, U6.48 (IOB_4a)
/BA: J1.b24, J5.b24, U8.39 (BA)
/BE: J1.a21, J5.a21, U8.35 (BE)
/BLUE: J8.3, R31.1, R35.1, R39.1
/CDONE: R1.2, U4.13 (IN), U6.7 (CDONE), U7.1 (1OE), U7.4 (2OE), U7.5 (13), U7.10 (3OE), U8.99 (P43)
/CLK: U8.36 (CLK), X2.3 (OUT)
/CTS: J2.4, U8.17 (P57)
/D0: J1.b15, J2.14, J5.b15, U6.23 (IOT_37a), U8.84 (D0)
/D1: J1.a15, J2.13, J5.a15, U6.25 (IOT_36b), U8.85 (D1)
/D2: J1.b16, J2.15, J5.b16, U6.26 (IOT_39a), U8.86 (D2)
/D3: J1.a16, J2.12, J5.a16, U6.27 (IOT_38b), U8.87 (D3)
/D4: J1.b17, J2.16, J5.b17, U6.28 (IOT_41a), U8.88 (D4)
/D5: J1.a17, J2.11, J5.a17, U6.31 (IOT_42b), U8.91 (D5)
/D6: J1.b18, J2.17, J5.b18, U6.32 (IOT_43a), U8.92 (D6)
/D7: J1.b19, J2.10, J5.b19, U6.34 (IOT_44b), U8.93 (D7)
/FCLK: U8.34 (FCLK), X3.3 (OUT)
/FPGA_MISO: R4.2, U6.17 (IOB_33b_SPI_SI), U7.12 (4A), U8.5 (P45)
/FPGA_MOSI: R3.2, U6.14 (IOB_32a_SPI_SO), U8.100 (P44)
/FPGA_SCK: R5.1, U6.15 (IOB_34a_SPI_SCK), U7.9 (3A), U8.74 (P72)
/G0: R27.2, U6.12 (IOB_22a)
/G1: R28.2, U6.21 (IOB_23b)
/G2: R29.2, U6.13 (IOB_24a)
/G3: R30.2, U6.20 (IOB_25b_G3)
/GREEN: J8.2, R22.1, R26.1, R30.1
/HSYNC: J8.13, U6.19 (IOB_29b)
/I2C_SCL: J1.a27, J2.25, J5.a27, U8.7 (P47)
/I2C_SDA: J1.a28, J2.24, J5.a28, U8.6 (P46)
/PHI2: J1.b1, J2.6, J5.b1, U4.2 (CLK/IN), U6.37 (IOT_45a_G1), U8.38 (PHI2)
/R0: R18.2, U6.6 (IOB_13b)
/R1: R19.2, U6.9 (IOB_16a)
/R2: R20.2, U6.10 (IOB_18a)
/R3: R21.2, U6.11 (IOB_20a)
/RED: J8.1, R13.1, R17.1, R21.1
/RTS: J2.5, U8.16 (P56)
/RUN: J1.a23, J5.a23, U8.32 (RUN)
/RXD: J2.3, U8.24 (P66)
/R/~W: J1.b25, J5.b25, U4.3 (IN), U6.40 (RGB1), U8.31 (~WE)
/SNES_CLK: J1.a30, J3.2, J4.2, J5.a30, U8.8 (P50)
/SNES_DATA0: J1.b27, J3.4, J5.b27, U8.10 (P52)
/SNES_DATA1: J1.b28, J4.4, J5.b28, U8.11 (P53)
/SNES_DATA2: J1.b29, J5.b29
/SNES_DATA3: J1.b30, J5.b30
/SNES_LATCH: J1.a29, J3.3, J4.3, J5.a29, U8.9 (P51)
/SYSCLK: U6.35 (IOT_46b_G0), X1.3 (OUT)
/TXD: J2.2, U8.25 (P67)
/VSYNC: J8.14, U6.18 (IOB_31b)
/~EXP: J1.a20, J5.a20, U8.82 (~CS6)
/~FLASH_SS: U4.12 (IN), U8.75 (P73)
/~FPGA_RES: R2.2, U6.8 (~CRESET), U8.98 (P42)
/~FPGA_SS: R6.2, U4.27 (I/O), U6.16 (IOB_35b_SPI_SS)
/~IRQ: J1.a24, J2.22, J5.a24, U8.97 (~IRQ)
/~I/O0: J2.21, U8.72 (~CS0)
/~I/O1: J1.b23, J5.b23, U6.41 (RGB2), U8.73 (~CS1)
/~NMI: J1.a26, J5.a26, U8.96 (~NMI)
/~RAM: J1.a22, J5.a22, U4.19 (I/O), U8.81 (~CS5)
/~RD: J1.b20, J2.7, J5.b20, U4.17 (I/O)
/~RES: J1.b2, J2.23, J5.b2, U8.26 (~RES)
/~ROMH: J1.b22, J5.b22, U4.5 (IN/PD), U8.83 (~CS7)
/~ROML: J1.b21, J5.b21, U4.4 (IN), U8.80 (~CS4)
/~SD_SS: U7.2 (1A), U8.18 (P60)
/~VIRQ: J1.a25, J5.a25, U6.3 (IOB_9b), U8.22 (P64)
/~WR: J1.a19, J2.20, J5.a19, U4.18 (I/O)
GND: C1.2, C2.2, C3.2, C4.2, C5.2, C7.2, C9.2, C10.2, C11.2, C12.2, C13.2, C14.2, C15.2, C16.2, C17.2, C18.2, C19.2, C20.2, C21.2, C22.2, C23.1, C24.2, H1.1, H2.1, H3.1, H4.1, J1.a1, J1.a18, J1.a32, J2.1, J3.7, J4.7, J5.a1, J5.a18, J5.a32, J7.3 (VSS), J7.6 (VSS), J7.12 (SHELL1), J7.13 (SHELL2), J8.0, J8.5, J8.6, J8.7, J8.8, J8.10, R5.2, R12.2, R13.2, R14.1, R22.2, R23.1, R31.2, R32.1, U4.8 (GND), U4.14 (GND), U4.15 (GND), U4.22 (GND), U5.2 (GND), U6.49 (GND), U7.7 (GND), U8.15 (VSS), U8.40 (VSS), U8.65 (VSS), U8.90 (VSS), X1.2 (GND), X2.2 (GND), X3.2 (GND)
unnamed: J7.1 (CD/DAT3), R8.2, U7.3 (1B)
unnamed: J7.5 (CLK), R12.1, U7.8 (3B)
unnamed: J7.2 (CMD), R9.2, U7.6 (2B)
unnamed: J7.7 (DAT0), R10.2, U7.11 (4B)
unnamed: J7.8 (DAT1), R7.2
unnamed: J7.9 (DAT2), R11.2
unnamed: R14.2, R15.2, R18.1
unnamed: R15.1, R16.2, R19.1
unnamed: R16.1, R17.2, R20.1
unnamed: R23.2, R24.2, R27.1
unnamed: R24.1, R25.2, R28.1
unnamed: R25.1, R26.2, R29.1
unnamed: R32.2, R33.2, R36.1
unnamed: R33.1, R34.2, R37.1
unnamed: R34.1, R35.2, R38.1
